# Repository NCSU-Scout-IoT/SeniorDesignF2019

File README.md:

# Scout IoT development kit
Table of Contents

Final Documents
- User Guides
  - QuickStart Guide
  - ESP32 AT Commands User Guide
  - Mobile Application User Guide
  - Software Guides
- Final Designs
  - Final Product Requirements
  - Final Test Plan with Results
  - Detailed Design Document
  - Final Bill of Materials
  - Final Product Price
  
Software Files
 - ESP32 Firmware
- Software Examples
- Mobile App Files

Hardware Files 
- EAGLE files
- Schematic and Board Layouts
- Enclosure 
  - SolidWorks Parts and Assembly
  - STL files

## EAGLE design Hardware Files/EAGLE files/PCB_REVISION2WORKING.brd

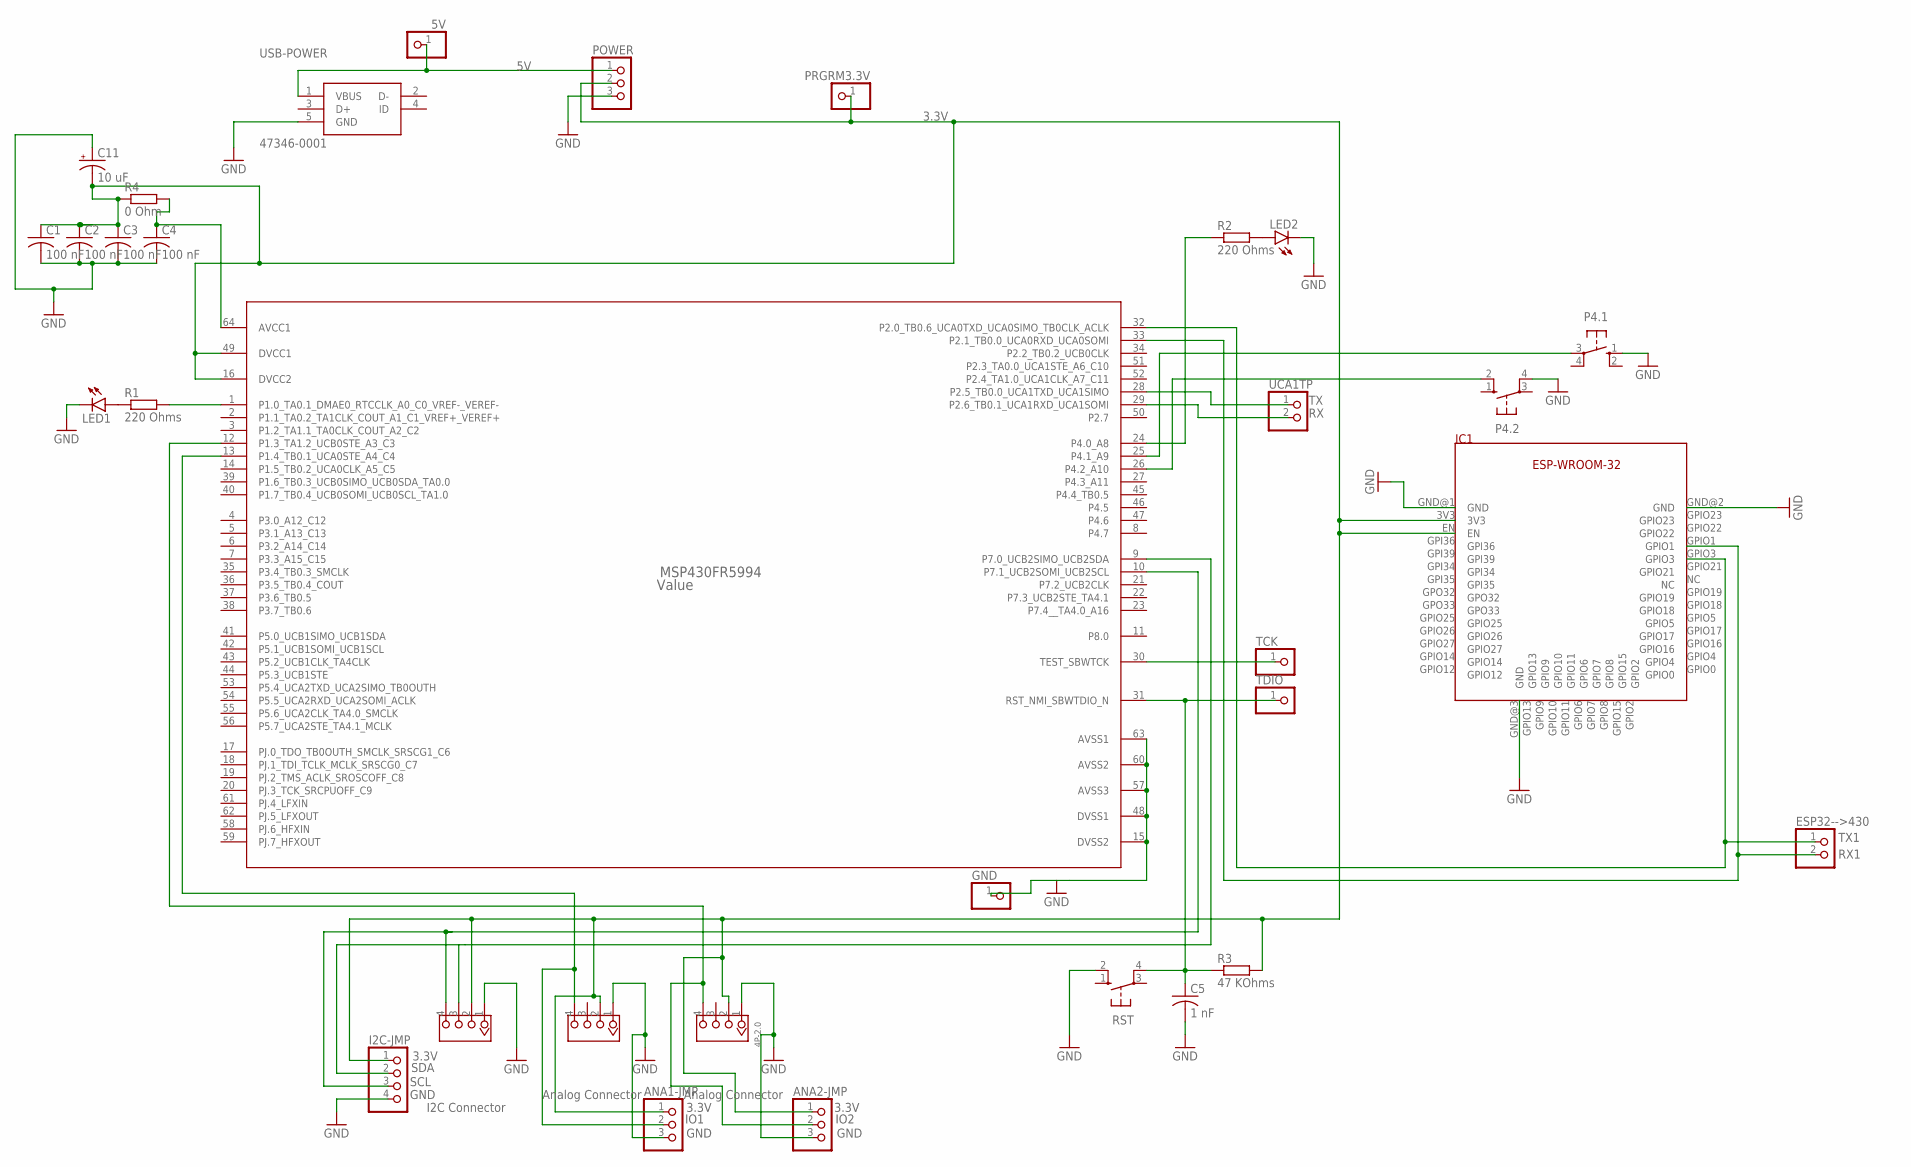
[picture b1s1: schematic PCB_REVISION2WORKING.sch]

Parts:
5V: PINHD-1X1; 1X01
ANA1-JMP, ANA2-JMP: PINHD-1X3; 1X03
ANALOG1, ANALOG2: 4P-2.0; HW4-2.0
C1, C2, C3, C4: 100 nF; C0805K
C5: 1 nF; C0805K
C11: 10 uF; E5-6
ESP32-->430: PINHD-1X2; 1X02
GND: PINHD-1X1; 1X01
I2C: 4P-2.0; HW4-2.0
I2C-JMP: PINHD-1X4; 1X04
IC1: ESPWROOM32
LED1, LED2: LED5MM
MSP430FR5994: Value; PM0064A_N
P4.1, P4.2: 10-XX; B3F-10XX
POWER: PINHD-1X3; 1X03
PRGRM3.3V: PINHD-1X1; 1X01
R1, R2: 220 Ohms; M1206
R3: 47 KOhms; M1206
R4: 0 Ohm; M1206
RST: 10-XX; B3F-10XX
TCK: PINHD-1X1; 1X01
TDIO: PINHD-1X1; 1X01
UCA1TP: PINHD-1X2; 1X02
USB-POWER: 47346-0001

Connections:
3.3V: ANA1-JMP.1, ANA2-JMP.1, ANALOG1.2, ANALOG2.2, C1.1, C2.1, C3.1, C11.-, I2C.2, I2C-JMP.1, IC1.3V3, IC1.EN, MSP430FR5994.16 (DVCC2), MSP430FR5994.49 (DVCC1), POWER.2, PRGRM3.3V.1, R3.2, R4.1
5V: 5V.1, POWER.1, USB-POWER.1 (VBUS)
GND: ANA1-JMP.3, ANA2-JMP.3, ANALOG1.1, ANALOG2.1, C1.2, C2.2, C3.2, C4.2, C5.2, C11.+, GND.1, I2C.1, I2C-JMP.4, IC1.GND@1 (GND), IC1.GND@2 (GND), IC1.GND@3 (GND), LED1.K (C), LED2.K (C), MSP430FR5994.15 (DVSS2), MSP430FR5994.48 (DVSS1), MSP430FR5994.57 (AVSS3), MSP430FR5994.60 (AVSS2), MSP430FR5994.63 (AVSS1), P4.1.1 (S), P4.2.4 (P1), POWER.3, RST.2 (S1), USB-POWER.5 (GND)
IO1: ANA1-JMP.2, ANALOG1.4, MSP430FR5994.13 (P1.4_TB0.1_UCA0STE_A4_C4)
IO2: ANA2-JMP.2, ANALOG2.4, MSP430FR5994.12 (P1.3_TA1.2_UCB0STE_A3_C3)
unnamed: LED1.A, R1.1
unnamed: LED2.A, R2.2
unnamed: MSP430FR5994.1 (P1.0_TA0.1_DMAE0_RTCCLK_A0_C0_VREF-_VER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), R1.2
unnamed: C5.1, MSP430FR5994.31 (RST_NMI_SBWTDIO_N), R3.1, RST.4 (P1), TDIO.1
unnamed: MSP430FR5994.25 (P4.1_A9), P4.1.3
unnamed: MSP430FR5994.26 (P4.2_A10), P4.2.2 (S1)
unnamed: MSP430FR5994.24 (P4.0_A8), R2.1
unnamed: C4.1, MSP430FR5994.64 (AVCC1), R4.2
unnamed: MSP430FR5994.30 (TEST_SBWTCK), TCK.1
RX: MSP430FR5994.29 (P2.6_TB0.1_UCA1RXD_UCA1SOMI), UCA1TP.2
RX1: ESP32-->430.2, IC1.GPIO1, MSP430FR5994.33 (P2.1_TB0.0_UCA0RXD_UCA0SOMI)
SCL: I2C.4, I2C-JMP.3, MSP430FR5994.10 (P7.1_UCB2SOMI_UCB2SCL)
SDA: I2C.3, I2C-JMP.2, MSP430FR5994.9 (P7.0_UCB2SIMO_UCB2SDA)
TX: MSP430FR5994.28 (P2.5_TB0.0_UCA1TXD_UCA1SIMO), UCA1TP.1
TX1: ESP32-->430.1, IC1.GPIO3, MSP430FR5994.32 (P2.0_TB0.6_UCA0TXD_UCA0SIMO_TB0CLK_ACLK)

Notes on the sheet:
I2C Connector
Analog Connector

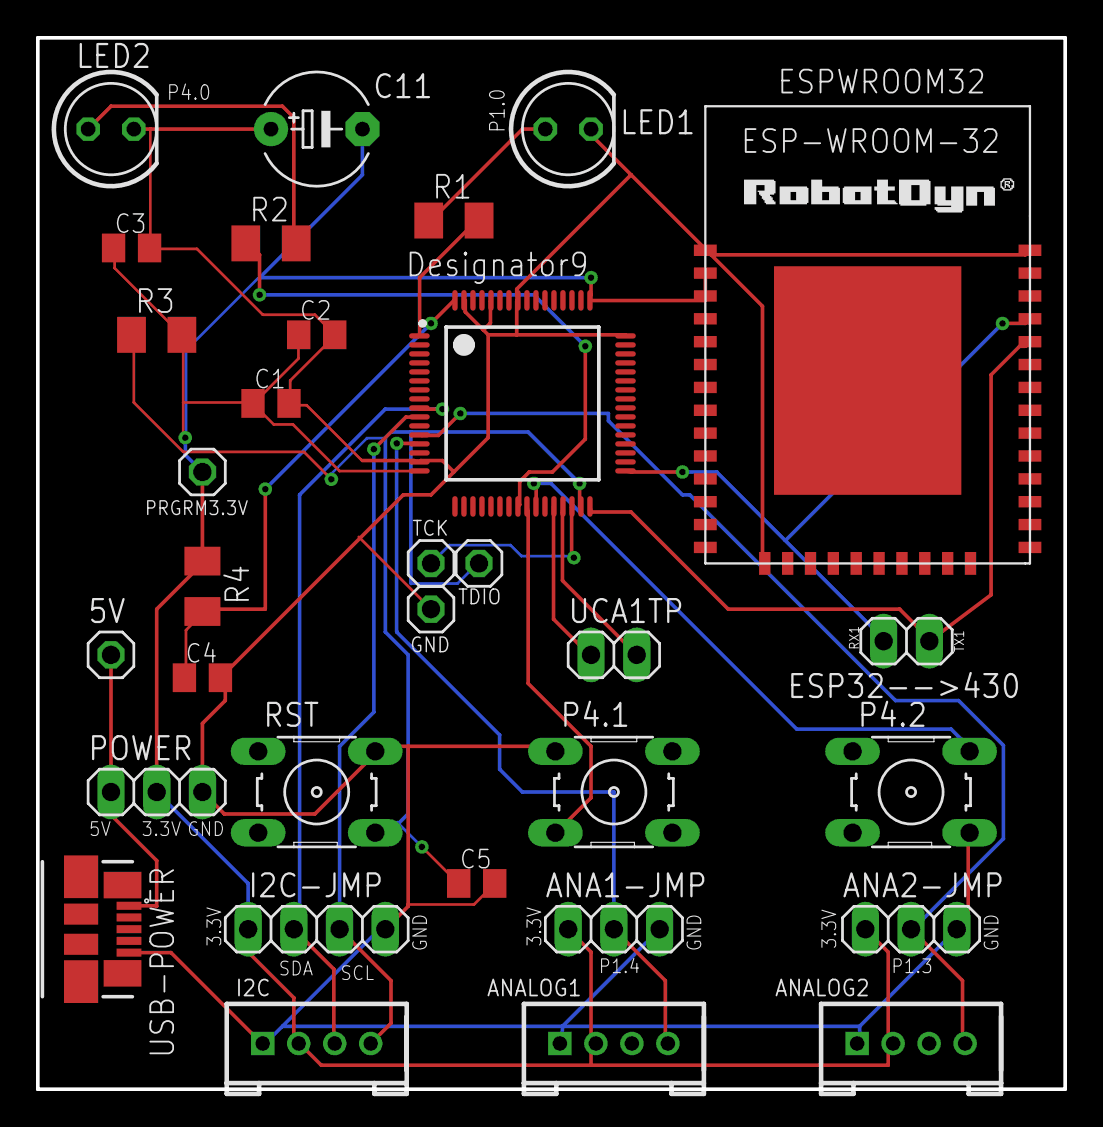
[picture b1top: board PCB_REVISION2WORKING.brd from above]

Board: 2 copper layers, 57.1 x 58.4 mm, 32 parts (0 on the bottom side), 20 nets.

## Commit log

2019-12-11 initial
2019-12-11 added more
2019-12-11 restructure
2019-12-11 restructure software
2019-12-11 added enclosure
2019-12-11 added docs
2019-12-12 Final commit
